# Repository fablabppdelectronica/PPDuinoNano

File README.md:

# MÓDULO EDUCATIVO: PPDuino Nano
## Presentación
Los módulos educativos son una herramienta invaluable para los estudiantes, que les permite aprender de forma tangible y efectiva los conocimientos de cada Unidad Didáctica.

El presente proyecto es una iniciativa innovadora que busca desarrollar un **módulo educativo de codigo abierto** que permitirá realizar los laboratorios de multiples unidades d

idáctica, que lo puedan fabricar los docentes o estudiantes y que permita trabajar con:
- Electrónica Analógica
- Electrónica Digital
- Electrónica Potencia
- Programación Embebida
- Redes
- Telecomunicaciones, entre otras.

El proyecto esta desarrollado por los docentes y estudiantes del Programa de Electronica Industrial.
## Proyecto PPDuino
Para esta primera etapa e inspirados por dispositivos PLCs como el S7-1200 y Logo de Siemens, el objetivo es disenar y fabricar un módulo educativo tipo PLC.

Se trabajara en 3 areas:
- Diseño Electronico.
- Diseño 2D y 3D.
- Programación.

Mostramos el bosquejo proyectado. 
<div></div>
Para conseguir el Producto Mínimo Viable, se siguieron la secuencia que se muestra en la imagen:
<div></div>

## Diseño Electrónico
### Tarjeta de procesador
Para el desarrollo de la tarjeta del procesador, se trabajo con la tarjeta Arduino Nano por su gran comunidad, facilidad de adquisión local y costo accesible.

#### Lista de componentes
<table><tr><th>Reference</th><td>Value</td><td>Footprint</td><td>Qty</td></tr><tr><th>A1</th><td>Arduino Nano</td><td>Module:Arduino_Nano</td><td>1</td></tr><tr><th>C1</th><td>100uF</td><td>Capacitor_THT:CP_Radial_D5.0mm_P2.50mm</td><td>1</td></tr><tr><th>C2</th><td>10uF</td><td>Capacitor_THT:CP_Radial_D5.0mm_P2.50mm</td><td>1</td></tr><tr><th>J1</th><td>PWR_IN</td><td>Borneras:TerminalBlock_Altech_AK300-2_P5.00mm</td><td>1</td></tr><tr><th>J2</th><td>Conn_01x12</td><td>Connector_PinSocket_2.54mm:PinSocket_1x12_P2.54mm_Horizontal</td><td>1</td></tr><tr><th>J11</th><td>INPUTS</td><td>Connector_PinSocket_2.54mm:PinSocket_1x10_P2.54mm_Vertical</td><td>1</td></tr><tr><th>J12</th><td>OUTPUTS</td><td>Connector_PinHeader_2.54mm:PinHeader_1x10_P2.54mm_Vertical</td><td>1</td></tr><tr><th>U1</th><td>L7805</td><td>Package_TO_SOT_THT:TO-220-3_Horizontal_TabDown</td><td>1</td></tr><tr><th>U6</th><td>+5V</td><td>Codigo_lib:Mini 560 Pro</td><td>1</td></tr></table>

#### Esquematico de procesador
<div></div>

### Entradas
### Tarjeta de entradas
Para el desarrollo de la tarjeta de entradas se diseño para proporcionar:
* 4 entradas digitales desde +5V a +24V (dependera del voltaje de alimentación)
* 2 entradas analogicas de 0V a +5V epcon la tarjeta Arduino Nano por su gran comunidad, facilidad de adquisión local y costo accesible.

#### Lista de componentes
<table><tr><th>Reference</th><td>Value</td><td>Footprint</td><td>Qty</td></tr><tr><th>D1</th><td>DI0</td><td>LED_THT:LED_D3.0mm_IRBlack</td><td>1</td></tr><tr><th>D2</th><td>DI1</td><td>LED_THT:LED_D3.0mm_IRBlack</td><td>1</td></tr><tr><th>D3</th><td>DI2</td><td>LED_THT:LED_D3.0mm_IRBlack</td><td>1</td></tr><tr><th>D4,D5</th><td>DI3</td><td>LED_THT:LED_D3.0mm_IRBlack</td><td>2</td></tr><tr><th>D6,D7</th><td>Z5.1V</td><td>Diode_THT:D_DO-35_SOD27_P7.62mm_Horizontal</td><td>2</td></tr><tr><th>J2</th><td>DI</td><td>Borneras:TerminalBlock_Altech_AK300-4_P5.00mm</td><td>1</td></tr><tr><th>J3</th><td>AI</td><td>Borneras:TerminalBlock_Altech_AK300-4_P5.00mm</td><td>1</td></tr><tr><th>J10</th><td>PWR_OUT</td><td>Borneras:TerminalBlock_Altech_AK300-2_P5.00mm</td><td>1</td></tr><tr><th>J11</th><td>INPUTS</td><td>Connector_PinHeader_2.54mm:PinHeader_1x10_P2.54mm_Vertical</td><td>1</td></tr><tr><th>Q1,Q2,Q3,Q4</th><td>BC548</td><td>Package_TO_SOT_THT:TO-92L_Inline_Wide</td><td>4</td></tr><tr><th>R1,R2,R3,R4,R5,<br>R6,R7,R8,R9,R10,<br>R11,R12,R14,<br>R15,R16,R17</th><td>2.2k</td><td>Resistor_THT:R_Axial_DIN0207_L6.3mm_D2.5mm_P7.62mm_Horizontal</td><td>16</td></tr><tr><th>R13</th><td>1k</td><td>Resistor_THT:R_Axial_DIN0207_L6.3mm_D2.5mm_P7.62mm_Horizontal</td><td>1</td></tr></table>

#### Esquematico de entradas
<div></div>

### Salidas
### Tarjeta de salidas
Para el desarrollo de la tarjeta del procesador, se tabajo con la tarjeta Arduino Nano por su gran comunidad, facilidad de adquisión local y costo accesible.

#### Lista de componentes
<table><tr><th>Reference</th><td>Value</td><td>Footprint</td><td>Qty</td></tr><tr><th>D5,J14</th><td>RLY0</td><td>Borneras:TerminalBlock_Altech_AK300-2_P5.00mm,LED_THT:LED_D3.0mm_IRBlack</td><td>2</td></tr><tr><th>D6,D8</th><td>1N4148</td><td>Diode_THT:D_DO-35_SOD27_P7.62mm_Horizontal</td><td>2</td></tr><tr><th>D7,J7</th><td>RLY1</td><td>Borneras:TerminalBlock_Altech_AK300-2_P5.00mm,LED_THT:LED_D3.0mm_IRBlack</td><td>2</td></tr><tr><th>D9</th><td>DI3</td><td>LED_THT:LED_D3.0mm_IRBlack</td><td>1</td></tr><tr><th>D10</th><td>DI2</td><td>LED_THT:LED_D3.0mm_IRBlack</td><td>1</td></tr><tr><th>D11</th><td>DI1</td><td>LED_THT:LED_D3.0mm_IRBlack</td><td>1</td></tr><tr><th>D12</th><td>DI0</td><td>LED_THT:LED_D3.0mm_IRBlack</td><td>1</td></tr><tr><th>J6</th><td>SEL0</td><td>Connector_PinHeader_2.54mm:PinHeader_1x03_P2.54mm_Vertical</td><td>1</td></tr><tr><th>J8</th><td>PWM</td><td>Borneras:TerminalBlock_Altech_AK300-4_P5.00mm</td><td>1</td></tr><tr><th>J9</th><td>PWR_OUT</td><td>Borneras:TerminalBlock_Altech_AK300-2_P5.00mm</td><td>1</td></tr><tr><th>J12</th><td>OUTPUTS</td><td>Connector_PinHeader_2.54mm:PinHeader_1x10_P2.54mm_Vertical</td><td>1</td></tr><tr><th>J13</th><td>SEL1</td><td>Connector_PinHeader_2.54mm:PinHeader_1x03_P2.54mm_Vertical</td><td>1</td></tr><tr><th>K1,K2</th><td>~</td><td>Codigo_lib:Relay</td><td>2</td></tr><tr><th>Q1,Q2</th><td>BC548</td><td>Package_TO_SOT_THT:TO-92L_Inline_Wide</td><td>2</td></tr><tr><th>R13,R14,R15,<br>R16,R17,R18,<br>R19,R20</th><td>330</td><td>Resistor_THT:R_Axial_DIN0207_L6.3mm_D2.5mm_P7.62mm_Horizontal</td><td>8</td></tr><tr><th>U5</th><td>L293D</td><td>Package_DIP:DIP-16_W7.62mm_LongPads</td><td>1</td></tr></table>

#### Esquematico de salidas
<div></div>

## Fabricacion
### Impresión 3D
<div></div>

<div></div>

<div></div>

### Fabricacion de PCB

<div></div>

## Programación
### Programación con Arduino IDE (C++)

Descarguemos el software para programar el Arduino Nano en [Descargar Arduino IDE](https://www.arduino.cc/en/software/)

Reconoscamos las herramientas de Arduino IDE
<div></div>

Seleccionar en BOARDS: Arduino Nano
Seleccionar en PORTS: COMx (Dependera del puerto asignado desde su computadora)
<div></div>

<div></div>

### Programación con OpenPLC IDE (Ladder)

Descarguemos el software OpenPLC para programar el Arduino Nano en [Descargar OpenPLC](https://autonomylogic.com/)

Reconoscamos las herramientas de OpenPLC
<div></div>

<div></div>

<div></div>

<div></div>

<div></div>

### Programación con Fab Blocks (Bloques)

Descarguemos el software Fab Blocks IDE para programar el Arduino Nano en [Descargar Fab Blocks IDE](https://github.com/codigospace/Fab-Blocks-IDE/releases)

Reconoscamos las herramientas de Fab Blocks IDE
<div></div>

<div></div>

<div></div>

<div></div>

# NOSOTROS
## IESTP Pedro P. Díaz
Somos el Instituto Superior Pedro P. Díaz de la cuidad de Arequipa en Perú, formamos profesionales que aportan desarrollo a la comunidad, región y pais.
Estamos ubicados en Arequipa, una cuidad cálida, rodeada de 3 volcanes, con una zona céntrica de arquitectura barroca construida de sillar, una piedra volcánica blanca, razon para denominarla "La Cuidad Blanca".
La instalación del instituto esta ubicada en Av. Pizarro 130 de Jose Luis Bustamante y Rivero.
## Programa de Electrónica Industrial
Somos el Programa de Electrónica Industrial del IESTP Pedro P. Diaz.
## Fab Lab PPD Electronica
Somos el laboratorio de fabricación digital del programa de Electrónica Industrial, que empodera a la comunidad educativa con capacitaciones y equipamiento para que fabriquen casi cualquier cosas.

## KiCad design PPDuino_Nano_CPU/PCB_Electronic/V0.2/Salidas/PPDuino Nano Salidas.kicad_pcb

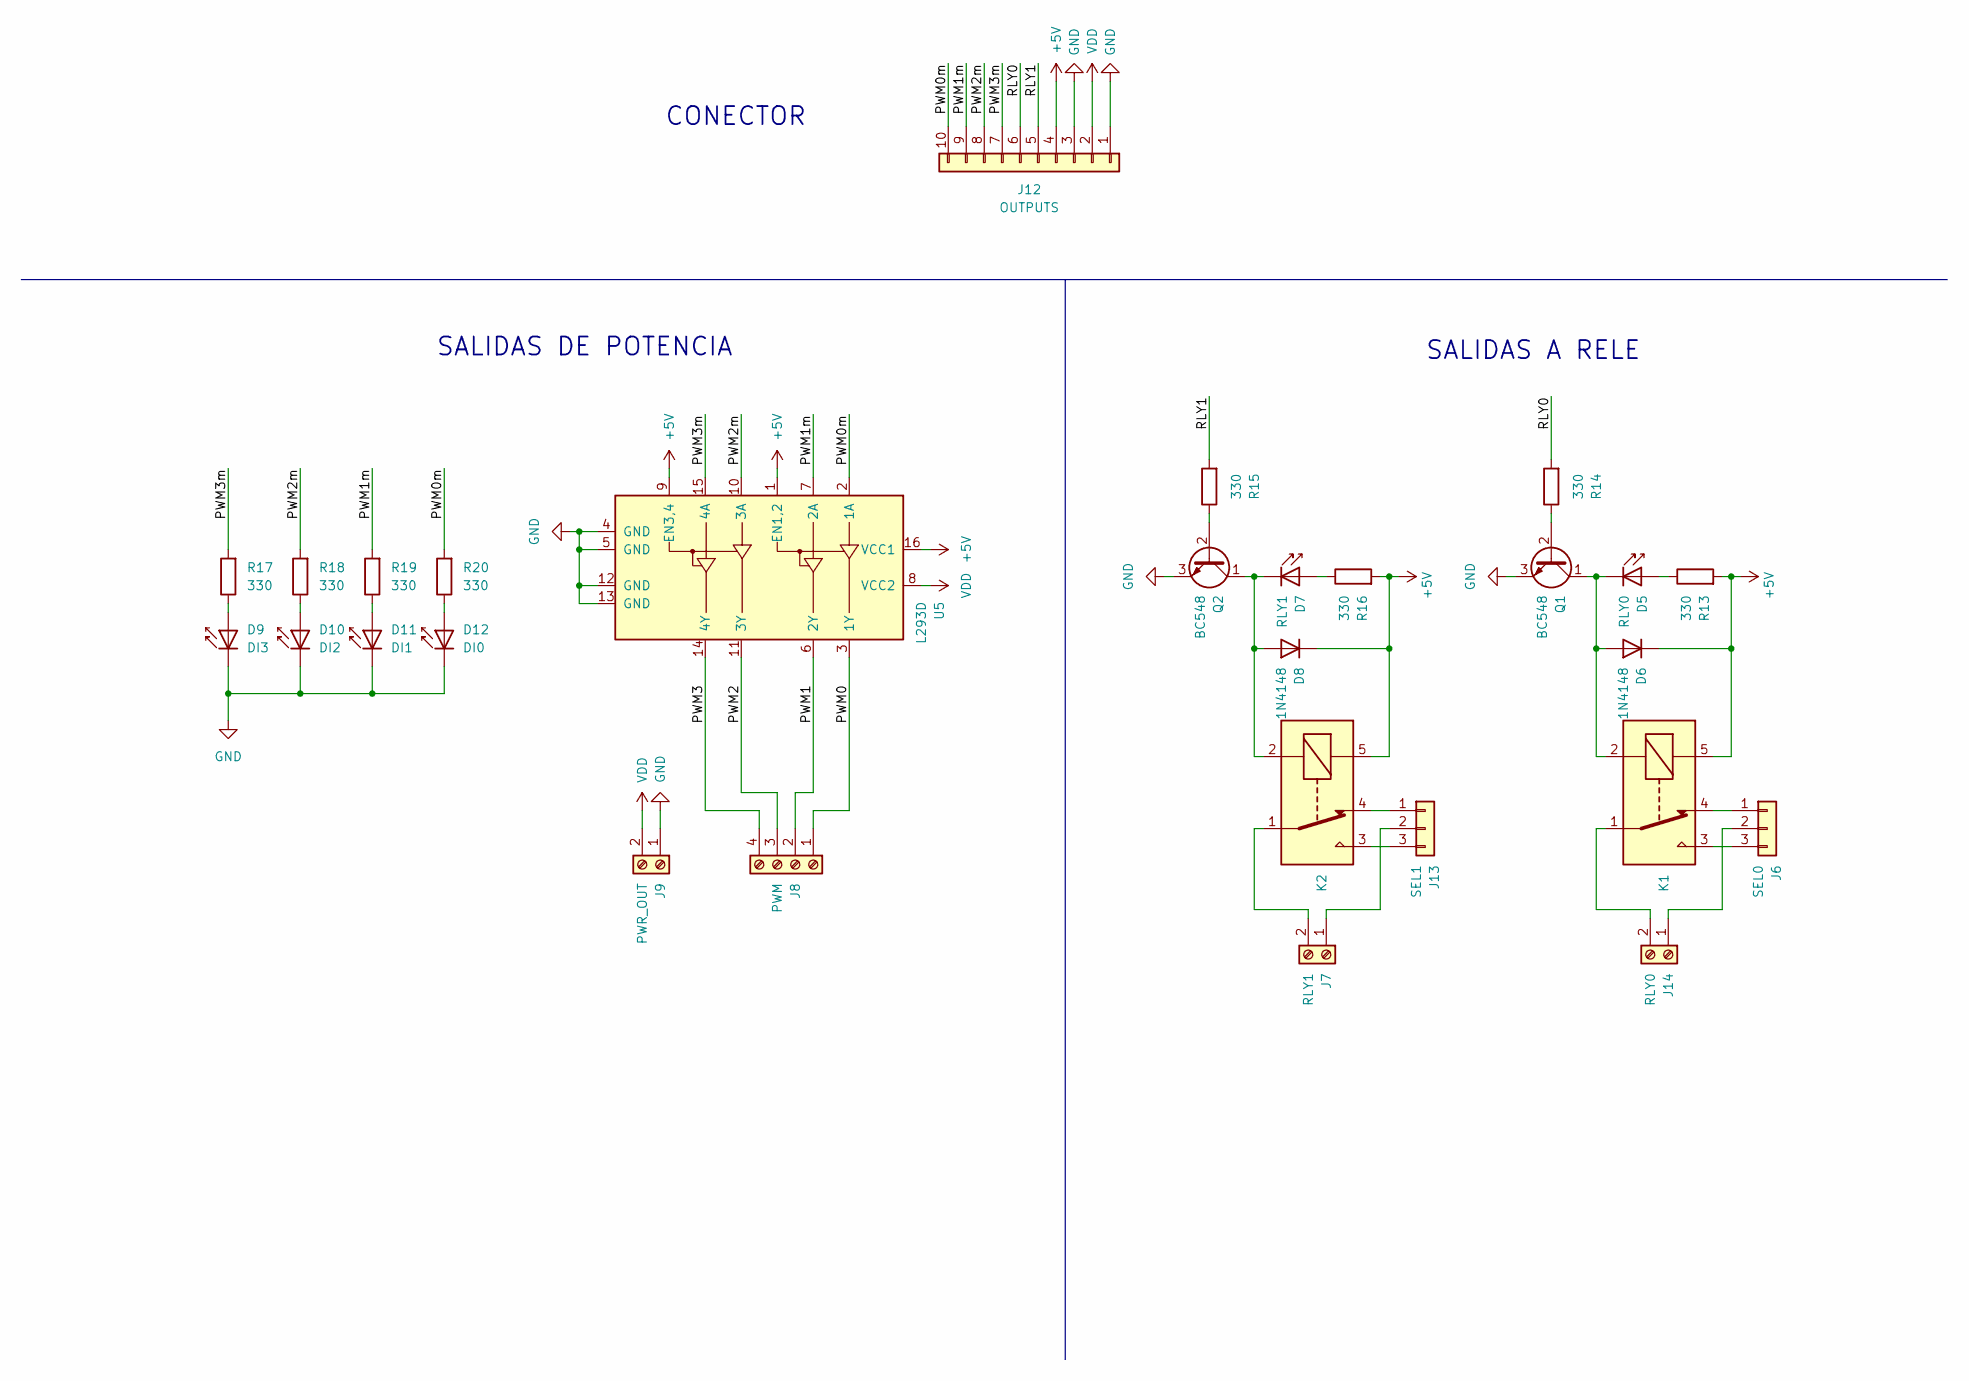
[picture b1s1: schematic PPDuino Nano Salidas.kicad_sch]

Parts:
D5: RLY0; LED_D3.0mm_IRBlack
D6, D8: 1N4148; D_DO-35_SOD27_P7.62mm_Horizontal
D7: RLY1; LED_D3.0mm_IRBlack
D9: DI3; LED_D3.0mm_IRBlack
D10: DI2; LED_D3.0mm_IRBlack
D11: DI1; LED_D3.0mm_IRBlack
D12: DI0; LED_D3.0mm_IRBlack
J6: SEL0; PinHeader_1x03_P2.54mm_Vertical
J7: RLY1; TerminalBlock_Altech_AK300-2_P5.00mm
J8: PWM; TerminalBlock_Altech_AK300-4_P5.00mm
J9: PWR_OUT; TerminalBlock_Altech_AK300-2_P5.00mm
J12: OUTPUTS; PinHeader_1x10_P2.54mm_Vertical
J13: SEL1; PinHeader_1x03_P2.54mm_Vertical
J14: RLY0; TerminalBlock_Altech_AK300-2_P5.00mm
K1, K2: Relay
Q1, Q2: BC548; TO-92L_Inline_Wide
R13, R14, R15, R16, R17, R18, R19, R20: 330; R_Axial_DIN0207_L6.3mm_D2.5mm_P7.62mm_Horizontal
U5: L293D; DIP-16_W7.62mm_LongPads

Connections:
+5V: D6.1 (K), D8.1 (K), J12.4, K1.5, K2.5, R13.2, R16.2, U5.1 (EN1,2), U5.9 (EN3,4), U5.16 (VCC1)
/PWM0: J8.1, U5.3 (1Y)
/PWM0m: J12.10, R20.2, U5.2 (1A)
/PWM1: J8.2, U5.6 (2Y)
/PWM1m: J12.9, R19.2, U5.7 (2A)
/PWM2: J8.3, U5.11 (3Y)
/PWM2m: J12.8, R18.2, U5.10 (3A)
/PWM3: J8.4, U5.14 (4Y)
/PWM3m: J12.7, R17.2, U5.15 (4A)
/RLY0: J12.6, R14.2
/RLY1: J12.5, R15.2
GND: D9.1 (K), D10.1 (K), D11.1 (K), D12.1 (K), J9.1, J12.1, J12.3, Q1.3 (E), Q2.3 (E), U5.4 (GND), U5.5 (GND), U5.12 (GND), U5.13 (GND)
unnamed: D5.2 (A), R13.1
unnamed: D5.1 (K), D6.2 (A), K1.2, Q1.1 (C)
unnamed: D7.2 (A), R16.1
unnamed: D7.1 (K), D8.2 (A), K2.2, Q2.1 (C)
unnamed: D9.2 (A), R17.1
unnamed: D10.2 (A), R18.1
unnamed: D11.2 (A), R19.1
unnamed: D12.2 (A), R20.1
unnamed: J6.1, K1.4
unnamed: J6.3, K1.3
unnamed: J7.2, K2.1
unnamed: J13.1, K2.4
unnamed: J7.1, J13.2
unnamed: J13.3, K2.3
unnamed: J6.2, J14.1
unnamed: J14.2, K1.1
unnamed: Q1.2 (B), R14.1
unnamed: Q2.2 (B), R15.1
VDD: J9.2, J12.2, U5.8 (VCC2)

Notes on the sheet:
SALIDAS DE POTENCIA
SALIDAS A RELE
CONECTOR

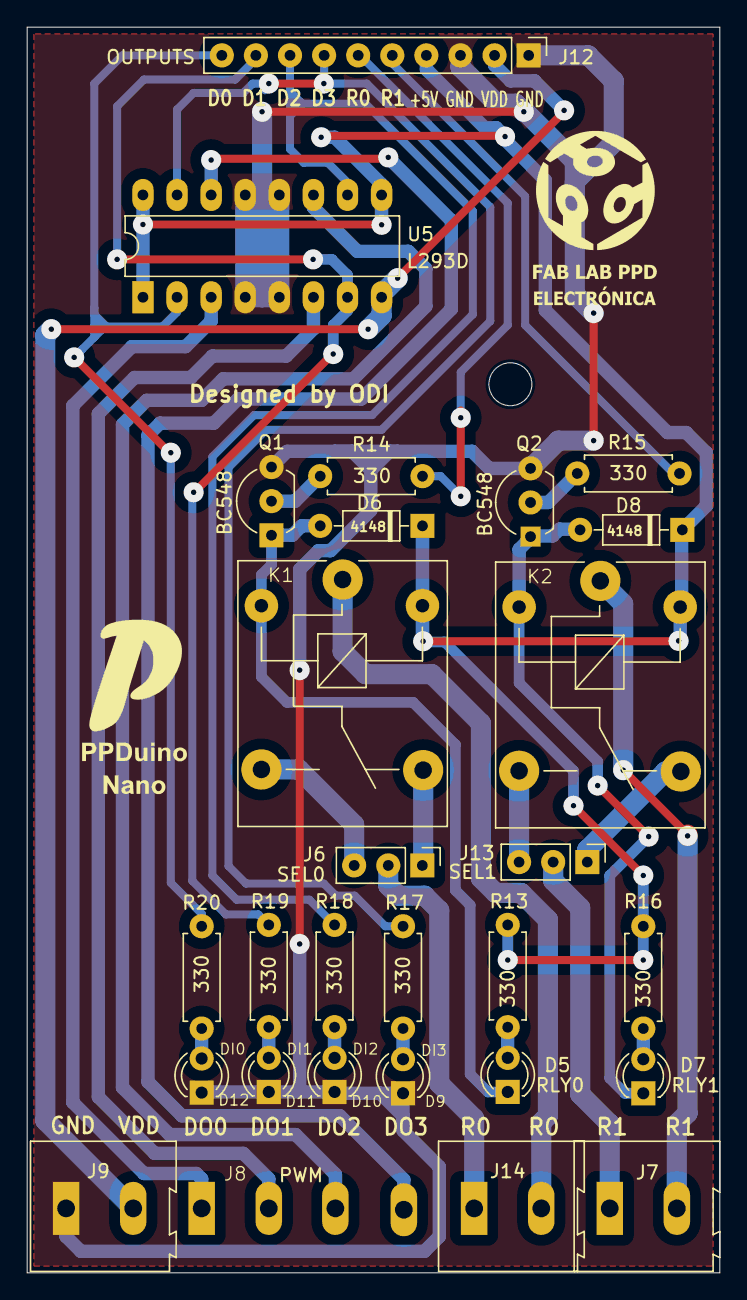
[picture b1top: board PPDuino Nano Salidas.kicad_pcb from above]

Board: 2 copper layers, 51.6 x 92.8 mm, 28 parts (0 on the bottom side), 31 nets.

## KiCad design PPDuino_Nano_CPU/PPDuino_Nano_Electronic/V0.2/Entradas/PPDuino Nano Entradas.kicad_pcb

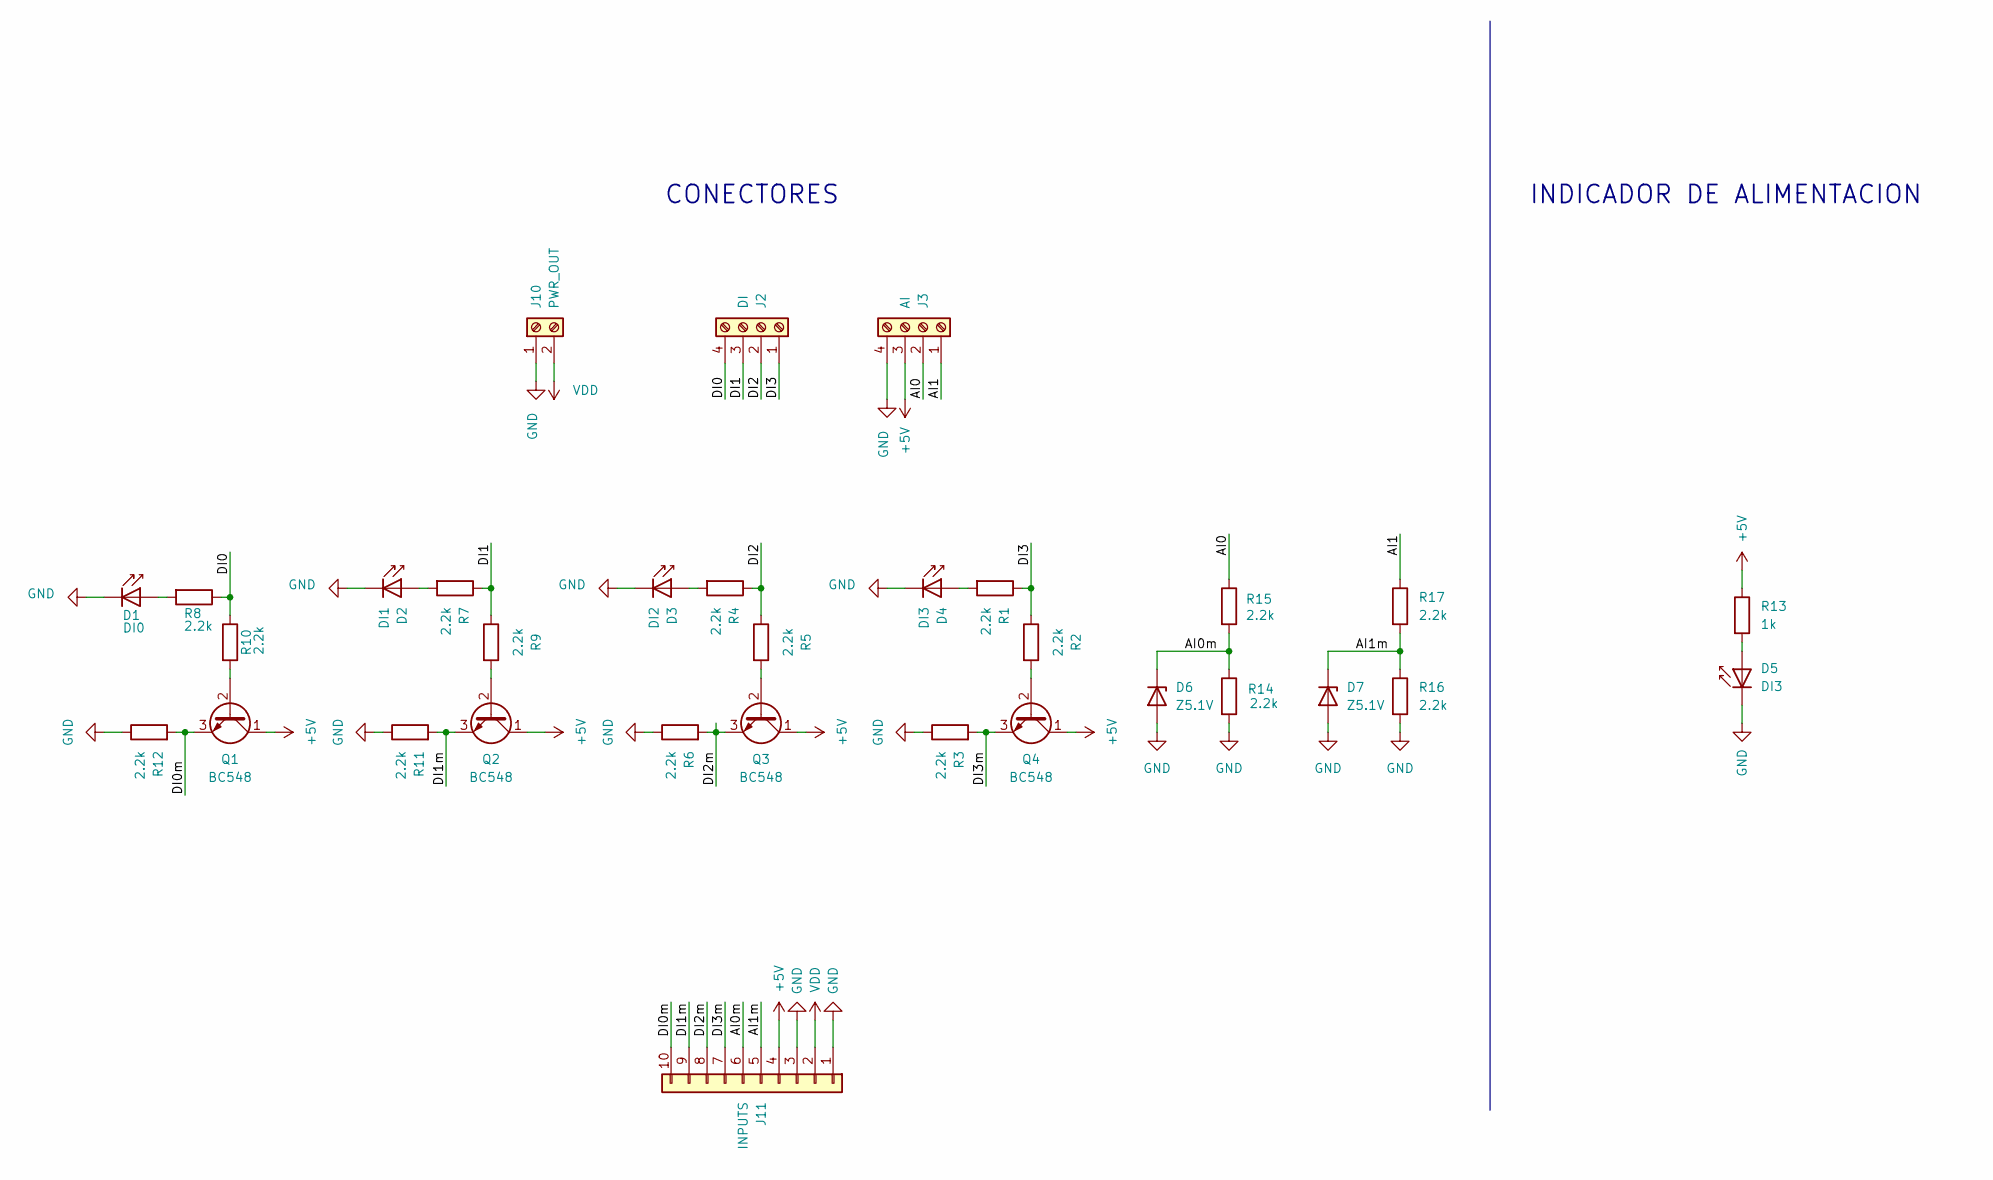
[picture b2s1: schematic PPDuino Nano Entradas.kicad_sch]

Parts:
D1: DI0; LED_D3.0mm_IRBlack
D2: DI1; LED_D3.0mm_IRBlack
D3: DI2; LED_D3.0mm_IRBlack
D4, D5: DI3; LED_D3.0mm_IRBlack
D6, D7: Z5.1V; D_DO-35_SOD27_P7.62mm_Horizontal
J2: DI; TerminalBlock_Altech_AK300-4_P5.00mm
J3: AI; TerminalBlock_Altech_AK300-4_P5.00mm
J10: PWR_OUT; TerminalBlock_Altech_AK300-2_P5.00mm
J11: INPUTS; PinHeader_1x10_P2.54mm_Vertical
Q1, Q2, Q3, Q4: BC548; TO-92L_Inline_Wide
R1, R2, R3, R4, R5, R6, R7, R8, R9, R10, R11, R12, R14, R15, R16, R17: 2.2k; R_Axial_DIN0207_L6.3mm_D2.5mm_P7.62mm_Horizontal
R13: 1k; R_Axial_DIN0207_L6.3mm_D2.5mm_P7.62mm_Horizontal

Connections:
+5V: J3.3, J11.4, Q1.1 (C), Q2.1 (C), Q3.1 (C), Q4.1 (C), R13.1
/AI0: J3.2, R15.1
/AI0m: D6.1 (K), J11.6, R14.1, R15.2
/AI1: J3.1, R17.1
/AI1m: D7.1 (K), J11.5, R16.1, R17.2
/DI0: J2.4, R8.1, R10.1
/DI0m: J11.10, Q1.3 (E), R12.2
/DI1: J2.3, R7.1, R9.1
/DI1m: J11.9, Q2.3 (E), R11.2
/DI2: J2.2, R4.1, R5.1
/DI2m: J11.8, Q3.3 (E), R6.2
/DI3: J2.1, R1.1, R2.1
/DI3m: J11.7, Q4.3 (E), R3.2
GND: D1.1 (K), D2.1 (K), D3.1 (K), D4.1 (K), D5.1 (K), D6.2 (A), D7.2 (A), J3.4, J10.1, J11.1, J11.3, R3.1, R6.1, R11.1, R12.1, R14.2, R16.2
unnamed: D1.2 (A), R8.2
unnamed: D2.2 (A), R7.2
unnamed: D3.2 (A), R4.2
unnamed: D4.2 (A), R1.2
unnamed: D5.2 (A), R13.2
unnamed: Q1.2 (B), R10.2
unnamed: Q2.2 (B), R9.2
unnamed: Q3.2 (B), R5.2
unnamed: Q4.2 (B), R2.2
VDD: J10.2, J11.2

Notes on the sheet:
INDICADOR DE ALIMENTACION
CONECTORES

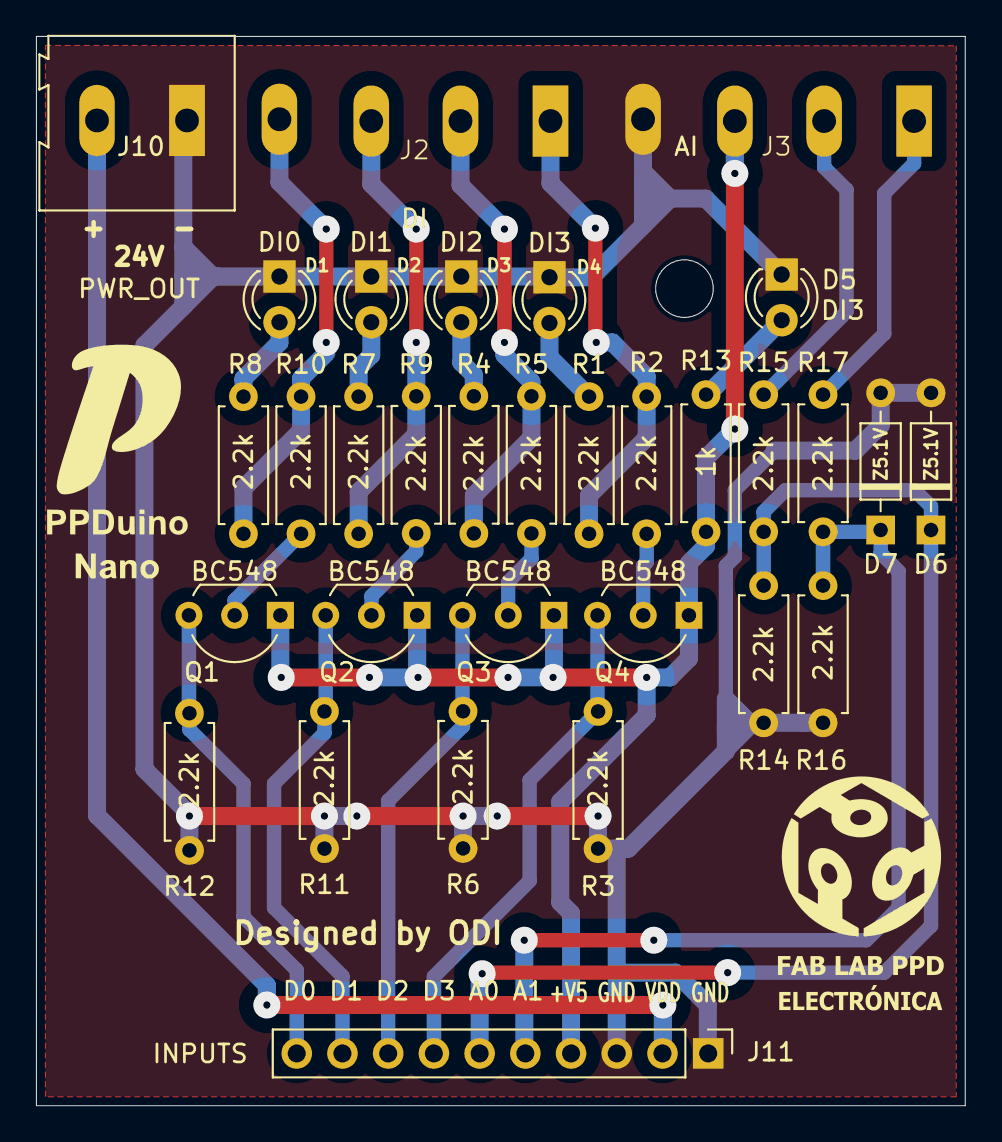
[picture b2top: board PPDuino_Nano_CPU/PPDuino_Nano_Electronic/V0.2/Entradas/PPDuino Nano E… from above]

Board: 2 copper layers, 51.6 x 59.4 mm, 32 parts (0 on the bottom side), 24 nets.

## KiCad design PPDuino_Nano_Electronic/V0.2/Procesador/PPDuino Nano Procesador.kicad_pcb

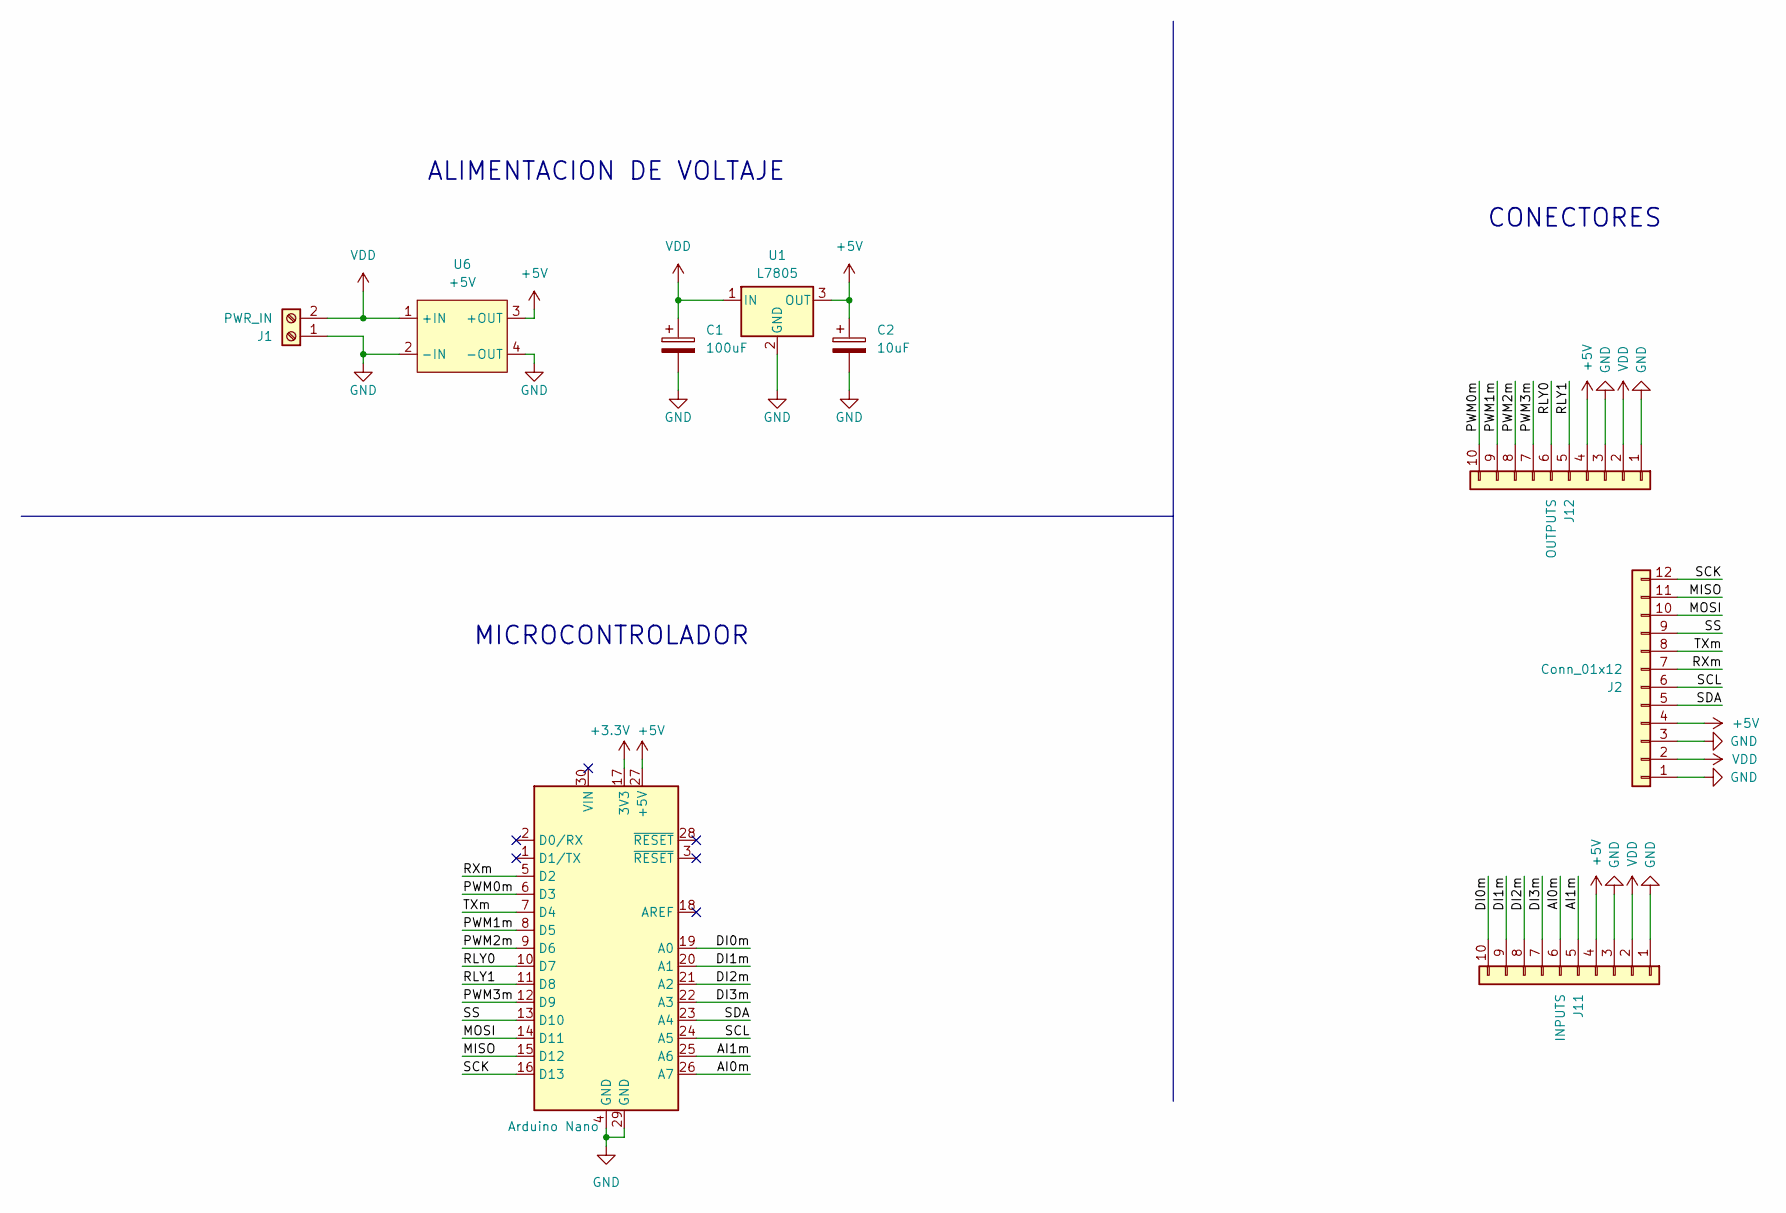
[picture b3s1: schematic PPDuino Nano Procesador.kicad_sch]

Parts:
A1: Arduino Nano; Arduino_Nano
C1: 100uF; CP_Radial_D5.0mm_P2.50mm
C2: 10uF; CP_Radial_D5.0mm_P2.50mm
J1: PWR_IN; TerminalBlock_Altech_AK300-2_P5.00mm
J2: Conn_01x12; PinSocket_1x12_P2.54mm_Horizontal
J11: INPUTS; PinSocket_1x10_P2.54mm_Vertical
J12: OUTPUTS; PinHeader_1x10_P2.54mm_Vertical
U1: L7805; TO-220-3_Horizontal_TabDown
U6: +5V; Mini 560 Pro

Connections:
+3.3V: A1.17 (3V3)
+5V: A1.27 (+5V), C2.1, J2.4, J11.4, J12.4, U1.3 (OUT), U6.3 (+OUT)
/AI0m: A1.26 (A7), J11.6
/AI1m: A1.25 (A6), J11.5
/DI0m: A1.19 (A0), J11.10
/DI1m: A1.20 (A1), J11.9
/DI2m: A1.21 (A2), J11.8
/DI3m: A1.22 (A3), J11.7
/MISO: A1.15 (D12), J2.11
/MOSI: A1.14 (D11), J2.10
/PWM0m: A1.6 (D3), J12.10
/PWM1m: A1.8 (D5), J12.9
/PWM2m: A1.9 (D6), J12.8
/PWM3m: A1.12 (D9), J12.7
/RLY0: A1.10 (D7), J12.6
/RLY1: A1.11 (D8), J12.5
/RXm: A1.5 (D2), J2.7
/SCK: A1.16 (D13), J2.12
/SCL: A1.24 (A5), J2.6
/SDA: A1.23 (A4), J2.5
/SS: A1.13 (D10), J2.9
/TXm: A1.7 (D4), J2.8
GND: A1.4 (GND), A1.29 (GND), C1.2, C2.2, J1.1, J2.1, J2.3, J11.1, J11.3, J12.1, J12.3, U1.2 (GND), U6.2 (-IN), U6.4 (-OUT)
VDD: C1.1, J1.2, J2.2, J11.2, J12.2, U1.1 (IN), U6.1 (+IN)

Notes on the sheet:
CONECTORES
MICROCONTROLADOR
ALIMENTACION DE VOLTAJE

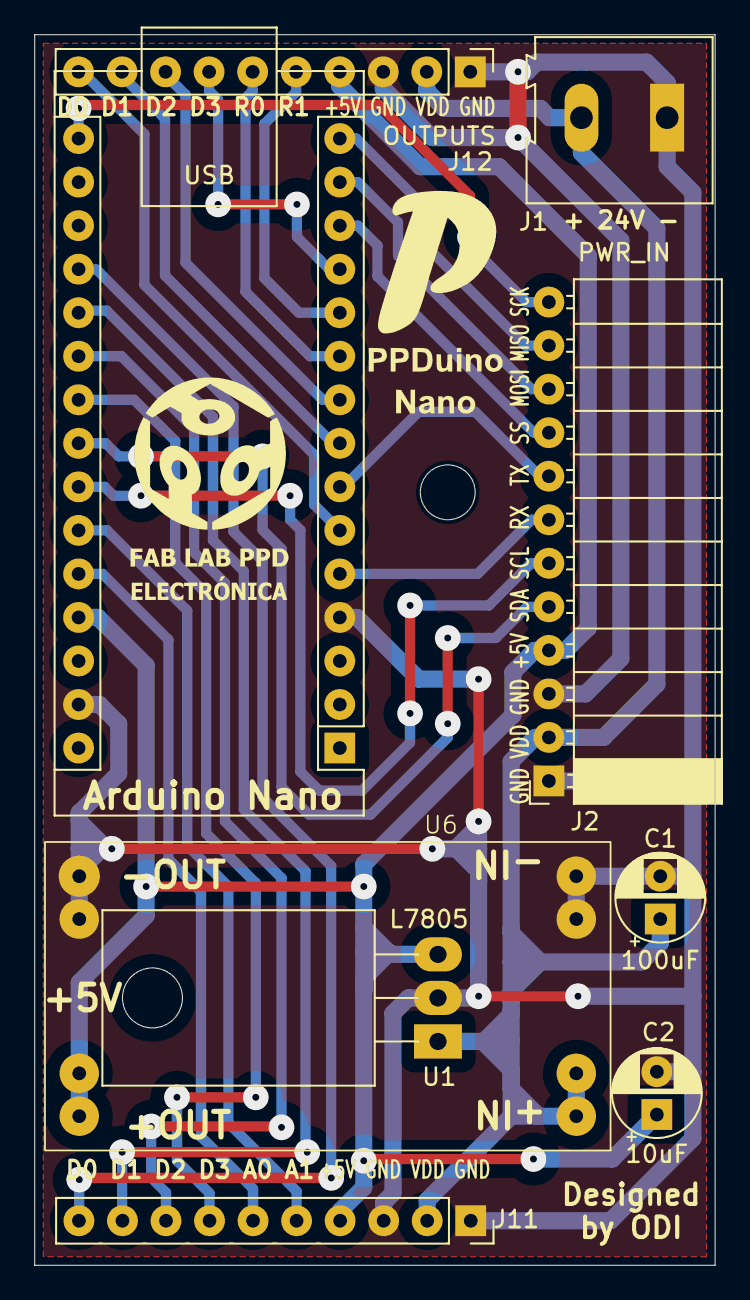
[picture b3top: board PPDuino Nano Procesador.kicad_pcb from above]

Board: 2 copper layers, 39.7 x 71.8 mm, 9 parts (0 on the bottom side), 23 nets.

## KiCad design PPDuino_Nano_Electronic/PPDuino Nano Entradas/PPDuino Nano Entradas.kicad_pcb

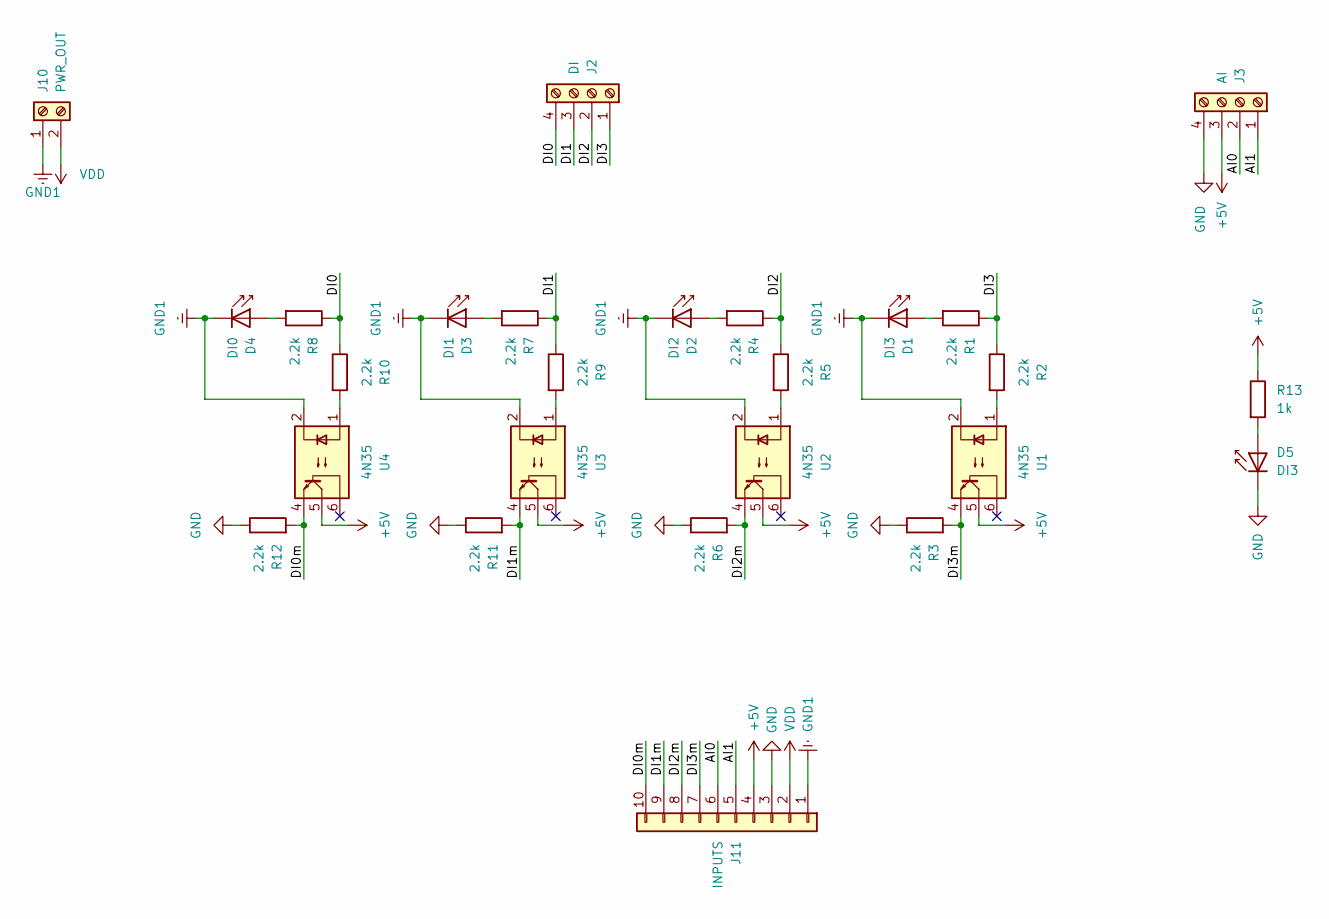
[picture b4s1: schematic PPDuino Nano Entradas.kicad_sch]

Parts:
D1, D5: DI3; LED_D3.0mm_IRBlack
D2: DI2; LED_D3.0mm_IRBlack
D3: DI1; LED_D3.0mm_IRBlack
D4: DI0; LED_D3.0mm_IRBlack
J2: DI; TerminalBlock_Altech_AK300-4_P5.00mm
J3: AI; TerminalBlock_Altech_AK300-4_P5.00mm
J10: PWR_OUT; TerminalBlock_Altech_AK300-2_P5.00mm
J11: INPUTS; PinHeader_1x10_P2.54mm_Vertical
R1, R2, R3, R4, R5, R6, R7, R8, R9, R10, R11, R12: 2.2k; R_Axial_DIN0207_L6.3mm_D2.5mm_P7.62mm_Horizontal
R13: 1k; R_Axial_DIN0207_L6.3mm_D2.5mm_P7.62mm_Horizontal
U1, U2, U3, U4: 4N35; DIP-6_W7.62mm_LongPads

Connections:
+5V: J3.3, J11.4, R13.1, U1.5, U2.5, U3.5, U4.5
/AI0: J3.2, J11.6
/AI1: J3.1, J11.5
/DI0: J2.4, R8.1, R10.1
/DI0m: J11.10, R12.2, U4.4
/DI1: J2.3, R7.1, R9.1
/DI1m: J11.9, R11.2, U3.4
/DI2: J2.2, R4.1, R5.1
/DI2m: J11.8, R6.2, U2.4
/DI3: J2.1, R1.1, R2.1
/DI3m: J11.7, R3.2, U1.4
GND: D5.1 (K), J3.4, J11.3, R3.1, R6.1, R11.1, R12.1
GND1: D1.1 (K), D2.1 (K), D3.1 (K), D4.1 (K), J10.1, J11.1, U1.2, U2.2, U3.2, U4.2
unnamed: D1.2 (A), R1.2
unnamed: D2.2 (A), R4.2
unnamed: D3.2 (A), R7.2
unnamed: D4.2 (A), R8.2
unnamed: D5.2 (A), R13.2
unnamed: R2.2, U1.1
unnamed: R5.2, U2.1
unnamed: R9.2, U3.1
unnamed: R10.2, U4.1
VDD: J10.2, J11.2

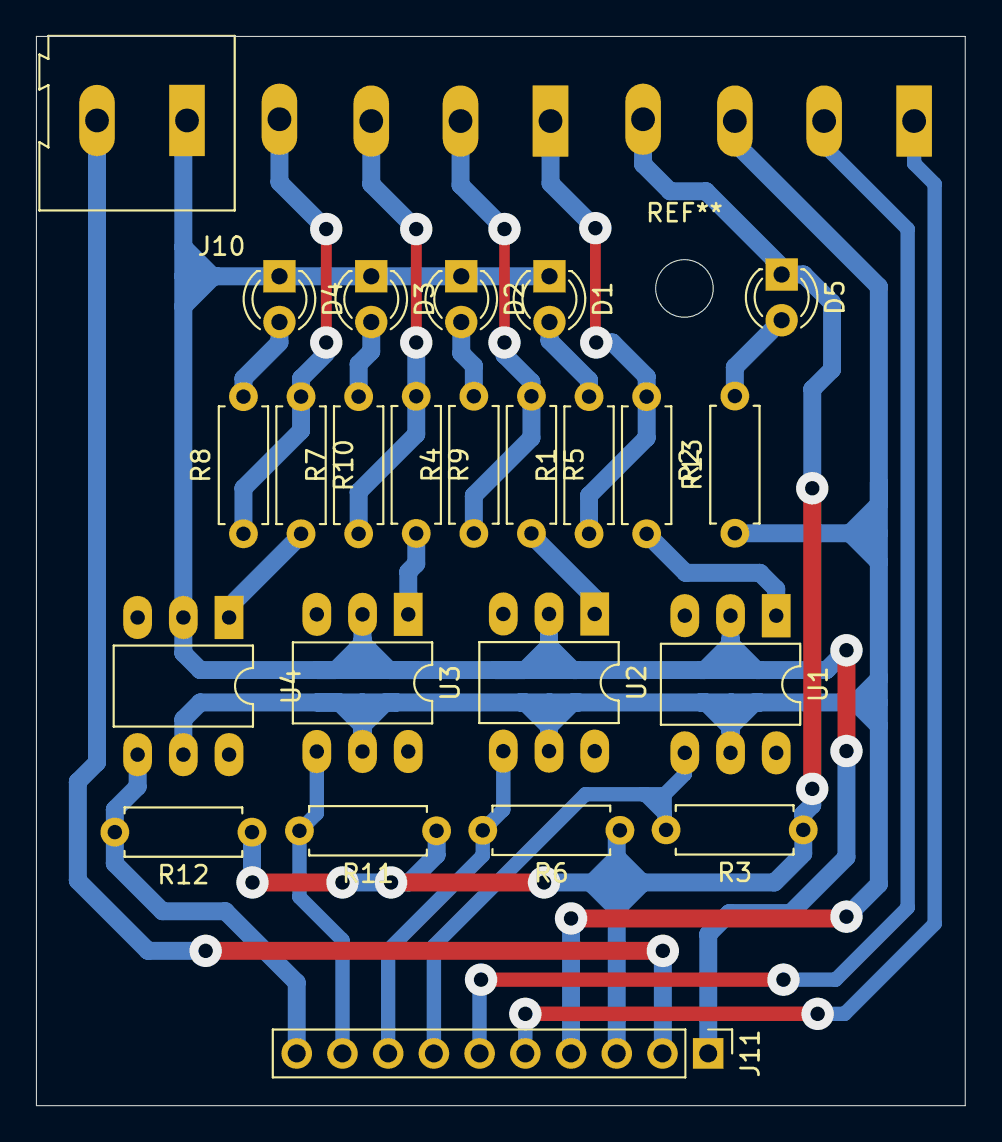
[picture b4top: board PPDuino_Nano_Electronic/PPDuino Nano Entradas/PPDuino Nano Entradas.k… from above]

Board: 2 copper layers, 51.6 x 59.4 mm, 26 parts (0 on the bottom side), 23 nets.

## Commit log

2024-12-06 Primer commit
2024-12-06 Organizado los archivo base iniciales
2024-12-06 Redactando Readme
2024-12-06 Redactando Readme2
2024-12-06 Mejorando Readme
2024-12-06 Mejorando Readme2
2024-12-06 Mejorando Readme3
2024-12-06 Presentando a Electronica
2024-12-06 Presentando a Electronica2
2024-12-06 Presentando a Electronica3
2024-12-06 Presentando a Electronica4
2024-12-06 Presentando a Electronica5
2024-12-06 Presentando a Electronica6
2024-12-06 Presentando a Electronica7
2024-12-06 Presentando a Electronica8
2024-12-06 Presentando a Electronica9
2024-12-06 Presentando a Electronica10
2025-07-18 Update 1
2025-07-18 PCB Complete
2025-07-21 Actualizar documentacion 1
2025-07-22 Actualizar documentacion 2
2025-07-22 Iniciante
2025-07-22 Iniciante 1
2025-07-22 Iniciante 2
2025-07-22 Iniciante 3
2025-07-22 Iniciante 4
2025-07-22 Iniciante 5
2025-07-22 Iniciante 6
2025-07-22 Iniciante 7
2025-07-22 Final
2025-07-22 Final 3D
2025-07-22 Final 3D 1
2025-07-25 Actualizando
2025-07-25 Actualizando 1
2025-07-25 Actualizando 3
2025-07-25 Actualizando 4
2025-07-25 Actualizando 5
2025-08-04 Actualizando datos
2025-08-04 Actualizando datos 2
2025-08-04 Actualizando datos 3
2025-08-05 PCB V0.2
2025-08-13 Actualizando Arduino IDE
2025-08-13 Actualizando Pasos
2025-08-13 Actualizando programacion
2025-09-18 Tabla Procesador
2025-09-18 Tabla Procesador2
2025-09-18 Tabla entrada
2025-09-18 Tabla entrada2
2025-09-18 Tabla salida
2025-09-18 Tabla entrada png
2025-09-18 Tabla procesador png
2025-09-18 Tabla procesador png 2
2025-09-18 Tabla procesador png 3
2025-09-19 All updated
2025-09-22 All updated 2
2025-09-22 All updated 3
2025-09-22 All updated 4
2025-09-22 All updated 5
2025-09-22 Update the modulo wifi
2025-09-23 Update the modulo wifi 2
2025-09-26 Updated 1
2025-09-26 Updated 2
2025-09-26 Updated 3
